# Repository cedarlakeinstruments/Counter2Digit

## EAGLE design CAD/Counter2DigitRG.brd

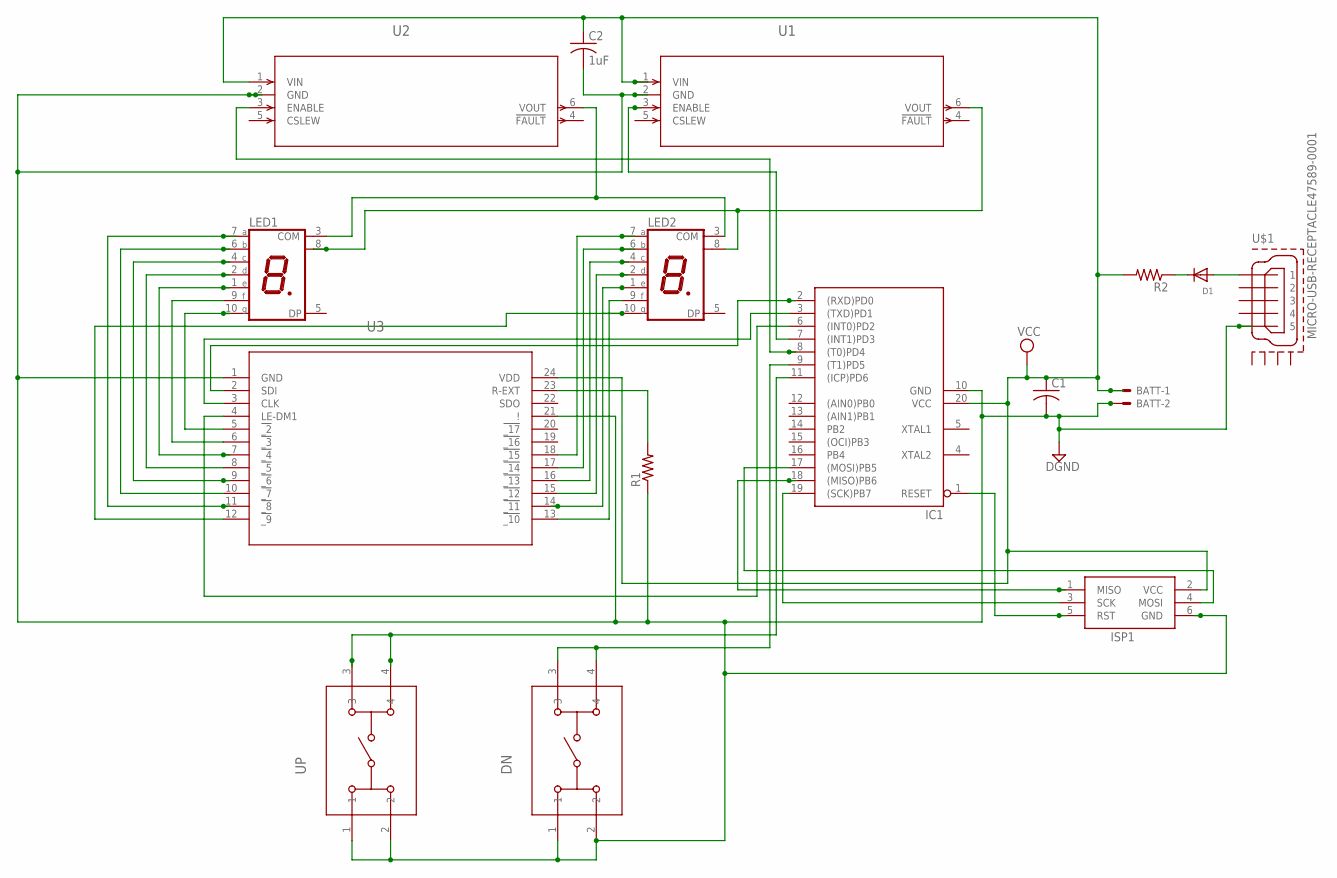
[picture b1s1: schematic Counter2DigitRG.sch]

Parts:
BATT: 22-23-2021
C1: C-USC0805; C0805
C2: 1uF; C0805
D1: DIODESOD-123; SOD-123
DN: 1-1825910-4; SW4_1825910-D
IC1: AT90S2313S; SO20L
ISP1: AVRISP-6; AVRISP
LED1, LED2: 7-SEG_SA56-11; SA56-11
R1, R2: R-US_M0805; M0805
U1, U2: MIC2005A-2YM6-TR; SOT-23-6_M6
U3: STP16CPC26MTRSO-24-M; SO-24-M
U$1: MICRO-USB-RECEPTACLE47589-0001; 47589-0001
UP: 1-1825910-4; SW4_1825910-D

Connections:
DGND: BATT.2, C1.2, C2.2, DN.1, DN.2, IC1.10 (GND), ISP1.6 (GND), R1.1, U1.2 (GND), U2.2 (GND), U3.1 (GND), U3.21 (!), U$1.5, UP.1, UP.2
unnamed: LED2.2 (D), U3.15 (!_12)
unnamed: LED1.3 (COM), LED2.3 (COM), U2.6 (VOUT)
unnamed: IC1.6 ((INT0)PD2), U3.4 (LE-DM1)
unnamed: LED1.8 (COM), LED2.8 (COM), U1.6 (VOUT)
unnamed: DN.3, DN.4, IC1.9 ((T1)PD5)
unnamed: IC1.11 ((ICP)PD6), UP.3, UP.4
unnamed: R1.2, U3.23 (R-EXT)
unnamed: IC1.2 ((RXD)PD0), U3.2 (SDI)
unnamed: IC1.3 ((TXD)PD1), U3.3 (CLK)
unnamed: IC1.18 ((MISO)PB6), ISP1.1 (MISO)
unnamed: IC1.7 ((INT1)PD3), U1.3 (ENABLE)
unnamed: IC1.8 ((T0)PD4), U2.3 (ENABLE)
unnamed: IC1.1 (RESET), ISP1.5 (RST)
unnamed: IC1.19 ((SCK)PB7), ISP1.3 (SCK)
unnamed: IC1.17 ((MOSI)PB5), ISP1.4 (MOSI)
unnamed: LED2.9 (F), U3.13 (!_10)
unnamed: LED1.10 (G), U3.5 (!_2)
unnamed: LED1.9 (F), U3.6 (!_3)
unnamed: LED1.1 (E), U3.7 (!_4)
unnamed: LED1.2 (D), U3.8 (!_5)
unnamed: LED1.4 (C), U3.9 (!_6)
unnamed: LED1.6 (B), U3.10 (!_7)
unnamed: LED1.7 (A), U3.11 (!_8)
unnamed: LED2.10 (G), U3.12 (!_9)
unnamed: LED2.1 (E), U3.14 (!_11)
unnamed: LED2.4 (C), U3.16 (!_13)
unnamed: LED2.6 (B), U3.17 (!_14)
unnamed: LED2.7 (A), U3.18 (!_15)
unnamed: D1.A, U$1.1
unnamed: D1.C, R2.1
VCC: BATT.1, C1.1, C2.1, IC1.20 (VCC), ISP1.2 (VCC), R2.2, U1.1 (VIN), U2.1 (VIN), U3.24 (VDD)

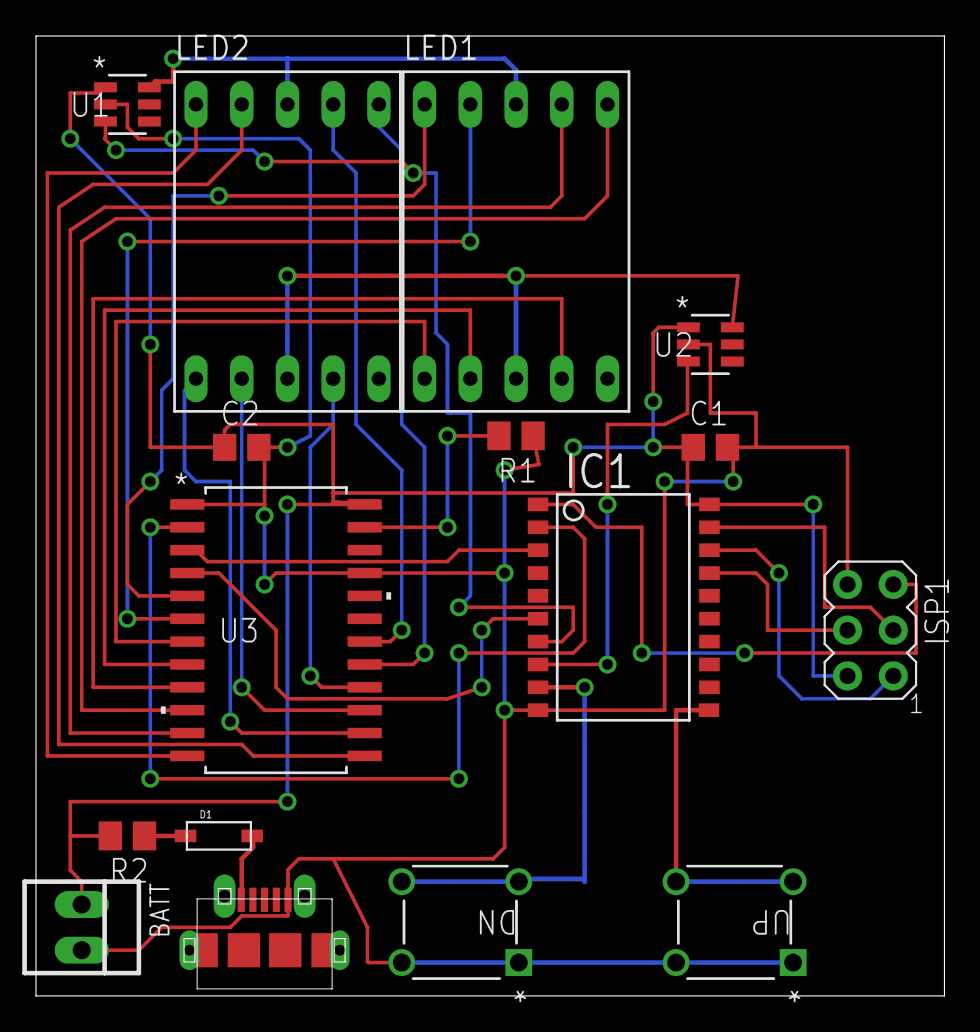
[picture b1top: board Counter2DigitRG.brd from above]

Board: 2 copper layers, 50.5 x 53.3 mm, 16 parts (0 on the bottom side), 32 nets.

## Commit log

2020-05-15 moving to win10

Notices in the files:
parts and their libraries:
con-molex-usb: (C) 2014 Tomasz Boleslaw CEDRO, cederom@tlen.pl, http://www.tomek.cedro.info.
COPYRIGHT: Copyright (C) 2018 Accelerated Designs. All rights reserved
COPYRIGHT: Copyright (C) 2016 Accelerated Designs. All rights reserved
